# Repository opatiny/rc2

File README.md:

# Remote Control Cylinder

---
Link to "site": https://opatiny.github.io/rc2/.

__WARNING:__ This README is not the main source of information for this project. A detailled paper can be found [here](https://github.com/opatiny/rc2/blob/master/documentation/RemoteControlCylinder.pdf).

_Final cylinder prototype_

## Cite this repository

Océane Patiny, & Luc Patiny. (2020, October 3). opatiny/rc2: Remote controlled cylinder final documentation (Version v1.0.0). Zenodo. http://doi.org/10.5281/zenodo.4064763

## Abstract
This one year project consists in the development of a remote controlled cylinder that uses servo motors to displace its center of mass, which leads the cylinder to accelerate linearly. This implies that very diversified fields such as mathematics, physics, programming, electronics and mechanics had to be explored and partly understood to be combined in the final prototype. This prototype has an acrylic glass base structure with a diameter of 32 cm, it is controlled using a C.H.I.P. Pro (a micro-controller similar to Raspberry Pi) and a customized dedicated extension board. The board includes a driver for four servo motors and a 6 axis accelerometer. Finally, the power supply consists of a pack of three AA batteries. All the programming was made using JavaScript scripts that are run using Node.js and a Shell. In addition, the cylinder is remotely controlled through a web page, which make it easy and intuitive for the user. The final features of this robotic cylinder are the following: it can roll forwards and backwards, stop and keep itself balanced on a gentle slope . Also, it is only working well on flat, hard surfaces, though it could easily be adapted to rougher surfaces. The possibility has also been considered of creating a sphere that uses the same technologies as the cylinder that was constructed in this project. The results of the project can be seen easily in [this movie](https://youtu.be/QggOjoGjJhA).

## Liscence

Finally, this work is meant to be as open-source as possible. Therefore, the software that was developed is under MIT licence, whereas the hardware is under CERN OHL.

## Concept

Initially the project was inspired by a rover realized by [Octanis](https://www.octanis.org/), a student's association specialized in electronics. The rover was supposed to be send to Antarctica and be able to analyse it's environment autonomously. Seeing the Rover tested on a Glacier on a windy day made me wonder what would be the best design for a windproof robot and I immediately thought of a spherical robot. However, once I got back home and looked for similar ideas, I realized that they were already existing projects that consisted in a spherical robot. One of the most famous being the [Sphero](https://www.sphero.com/), a spherical robot toy.

Looking further, I also realized that most of the projects use a similar approach to move the sphere: I call it the hamster wheel approach. It basically is a little car which wheels lay on the outer, rigid shell that induces the movement. I, on the contrary, had imagined a completely different system: I would displace the center of mass of the cylinder to make it roll.

## Programming

All the code that allows the control of the cylinder is contained in the following repository:
[https://github.com/opatiny/rpi-cylinder](https://github.com/opatiny/rpi-cylinder).

The programming has been done in JavaScript (using Node.js) and HTML for the web page that allows the control of the cylinder. Websocket was used to make the web page dynamic.

## Documentation

You can find a lot mor documentation about this project in the [documentation](https://github.com/opatiny/rc2/tree/master/documentation) section of this repository. There, you will find pictures, a developed abstract, and the paper about this project.

## Videos

Cardboard model of the cylinder's mechanism: [https://youtu.be/4SuPhpwOK5g](https://youtu.be/4SuPhpwOK5g)

The mass of cylinderPrototype2 moving on a circle using an atMega32u4: [https://youtu.be/1zOCNZ_r5pY](https://youtu.be/1zOCNZ_r5pY)

Final cylinder's prototype presentation video:
[https://youtu.be/QggOjoGjJhA](https://youtu.be/QggOjoGjJhA)

## Repository structure

In this section, we explain what the different folders of this repository contain and what it was used for.

__Note:__ Three main prototypes were built during this project. To refer to them, we use the acronyms cp1, cp2 and cp3 ("cp" stands for "cylinderPrototype"). You can see pictures of the prototypes in the [Pictures section](#pictures).

### arduino
Very basic programs in Arduino that allowed to test the movement of the mass with cp2. The values of the angles of the servos motors depending on the mass position were exported from the [GeoGebra model](https://github.com/opatiny/rc2/blob/master/movingMassOnCircle/geogebra/cylinderPrototype2/cylinderPrototype2.ggb) that we designed.

### datasheets
Datasheets of the electronical components used in this project: servo motors (MG995), accelerometer (MPU6050), servos driver (PCA9685) and C.H.I.P..

### documentation
Main source of information about this project, contains a pdf of the paper, a presentation, posters and an abstract. You will also find pictures there.

### freecad
FreeCAD is the software we used to create the designs of the cylinder. The "exports" subfolder contains files that can be directly used to laser cut the different parts (.dxf).

### javascript
First JavaScript programs that implemented the mathematical formula that returns the angles of the servos depending on the position of the mass. This code is the base of the [chip](https://github.com/opatiny/chip) GitHub repository, which contains the final code.

### movingMassOnCircle
Contains the GeoGebra models of the cylinder's mass movement and files commenting the observations made based upon them.

### pcb
Contains the Eagle and KiCAD files of the extension boards. They are two different boards, because when working on the project after a year, I realized that the cylinder was no longer functionning. I therefore had to change the micro-controller, because C.H.I.P. had made bankrupt. I decided to switch to a Raspberry Pi Nano W.

### raspberry
Procedure allowing to format a Raspberry Pi to make it act as a WiFi rooter.

## Pictures

Here are a few pictures of the project.

_Cardboard model of the cylinder_

_First prototype of the cylinder_

_[GeoGebra](https://www.geogebra.org/) model allowing to see the movement of the servo motors_

_Close-up of the second prototype_

_Metal turning a part of cp3_

_PCB extension allowing the connection of two I2C peripherals to the C.H.I.P. Pro (accelerometer and servo driver)_

_Long aperture picture of the mass moving on a spiral (cp3), max radius is 40mm_

_Final control web page_

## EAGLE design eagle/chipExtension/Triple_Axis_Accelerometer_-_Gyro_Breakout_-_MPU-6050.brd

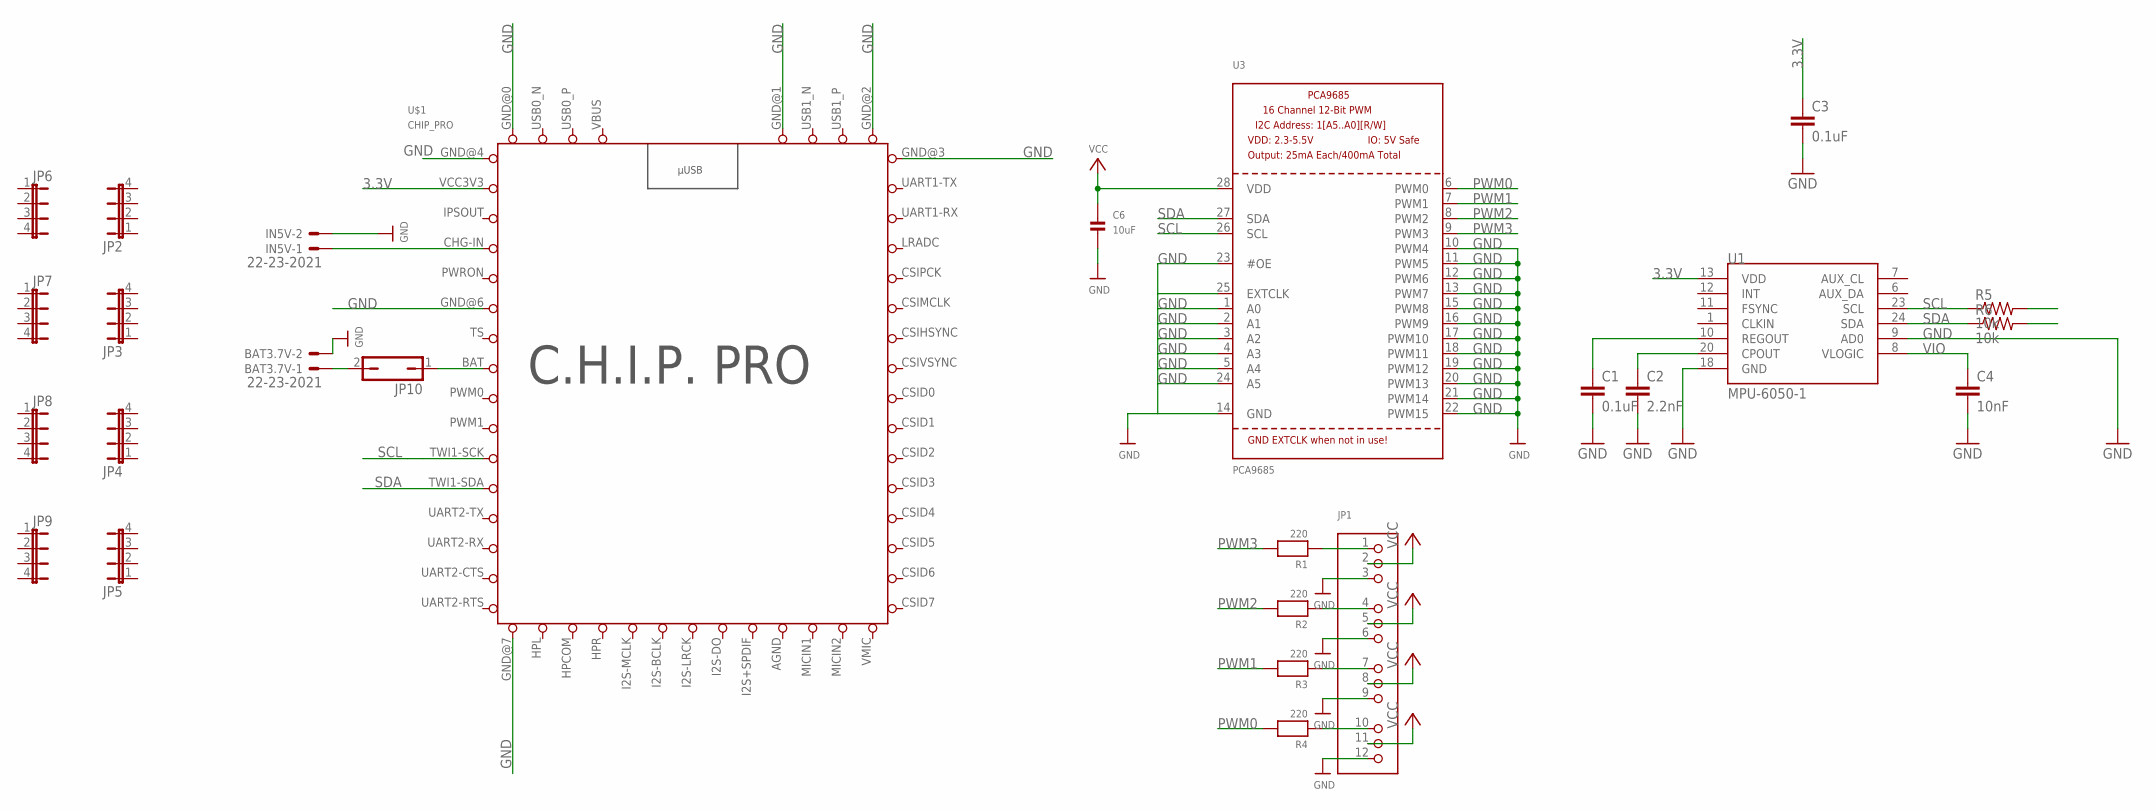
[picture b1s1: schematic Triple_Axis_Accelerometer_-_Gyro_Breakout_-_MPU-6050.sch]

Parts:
BAT3.7V: 22-23-2021
C1, C3: 0.1uF; 0603-CAP
C2: 2.2nF; 0603-CAP
C4: 10nF; 0603-CAP
C6: 10uF; 0805
IN5V: 22-23-2021
JP1: HEADER-3X04; 3X04
JP2, JP3, JP4, JP5, JP6, JP7, JP8, JP9: JP4E; JP4
JP10: JP1Q; JP1
R1, R2, R3, R4: 220; 0805
R5, R6: 10k; R0805
U1: MPU-6050-1; QFN-24-4MM2
U3: PCA9685; TSSOP28
U$1: CHIP_PRO

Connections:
3.3V: C3.1, U1.13 (VDD), U$1.VCC3V3
AGND: U$1.AGND
GND: BAT3.7V.2, C1.2, C2.2, C3.2, C4.2, C6.2, IN5V.2, JP1.3, JP1.6, JP1.9, JP1.12, U1.9 (AD0), U1.18 (GND), U3.1 (A0), U3.2 (A1), U3.3 (A2), U3.4 (A3), U3.5 (A4), U3.10 (PWM4), U3.11 (PWM5), U3.12 (PWM6), U3.13 (PWM7), U3.14 (GND), U3.15 (PWM8), U3.16 (PWM9), U3.17 (PWM10), U3.18 (PWM11), U3.19 (PWM12), U3.20 (PWM13), U3.21 (PWM14), U3.22 (PWM15), U3.23 (#OE), U3.24 (A5), U3.25 (EXTCLK), U$1.GND@0 (GND), U$1.GND@1 (GND), U$1.GND@2 (GND), U$1.GND@3 (GND), U$1.GND@4 (GND), U$1.GND@6 (GND), U$1.GND@7 (GND)
IPSOUT: U$1.IPSOUT
unnamed: JP1.1, R1.1
unnamed: JP1.4, R2.1
unnamed: C2.1, U1.20 (CPOUT)
unnamed: JP1.7, R3.1
unnamed: C1.1, U1.10 (REGOUT)
unnamed: JP1.10, R4.1
unnamed: IN5V.1, U$1.CHG-IN
PWM0: R4.2, U3.6 (PWM0)
PWM1: R3.2, U3.7 (PWM1)
PWM2: R2.2, U3.8 (PWM2)
PWM3: R1.2, U3.9 (PWM3)
SCL: R5.1, R5.2, U1.23 (SCL), U3.26 (SCL), U$1.TWI1-SCK
SDA: R6.1, R6.2, U1.24 (SDA), U3.27 (SDA), U$1.TWI1-SDA
VBUS: U$1.VBUS
VCC: BAT3.7V.1, C6.1, JP1.2, JP1.5, JP1.8, JP1.11, JP10.1, JP10.2, U3.28 (VDD), U$1.BAT
VIO: C4.1, U1.8 (VLOGIC)

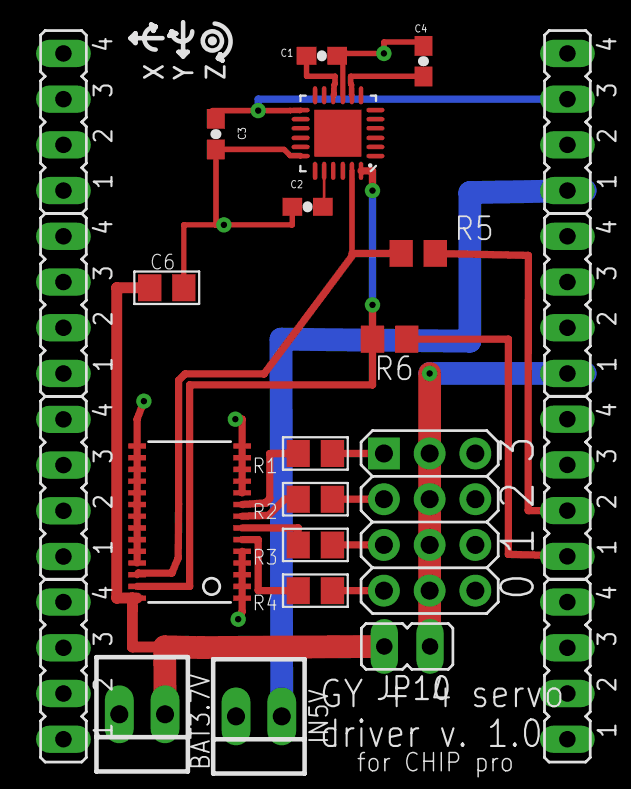
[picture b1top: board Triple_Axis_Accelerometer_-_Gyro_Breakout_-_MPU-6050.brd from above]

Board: 2 copper layers, 26 parts (1 on the bottom side), 17 nets.

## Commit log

2016-10-17 Datasheet MPU-6050 accelerometer - gyroscope
2016-10-17 Add initial freecad files
2016-10-17 Add servo oscilloscope
2016-10-19 Add high speed
2016-11-28 reorganising directories
2016-11-28 move files
2016-11-28 editing the readme
2016-11-28 readme changes
2016-12-19 Ordering directories
2016-12-19 add convert wolfram
2016-12-20 fix bug of ) ( not converted to ) * (
2016-12-30 working on code and adding .idea
2016-12-30 testing committing
2017-01-05 adding pictures
2017-01-16 modifing formula code
2017-01-18 modifing freecad document: wheel
2017-01-21 adding cylinder schemes in pictures
2017-01-29 modifing wheel and wheelAccessory (freecad)
2017-02-11 add gitignore file
2017-02-11 Remove unused files
2017-02-11 Add test code for understand code
2017-02-11 trying to understand formulas in code
2017-02-13 new formula taken from wolfram
    the thee other ones are when the general signs varies and when the sign in the cos varies
2017-02-22 adding links to the README
2017-02-24 Ordering pictures
2017-04-03 Adding new geogebra file. This is a first test of sovling the angles of the servo depending on the mass position, graphicaly.
2017-04-03 Adding datasheets
2017-04-05 Working on servosMovement
2017-04-05 Developing servos angles depending on position of the mass
2017-04-05 Adding "mess".
2017-04-08 First working moving servos
2017-04-10 Evolving servoMovement and adding pictures
2017-04-10 Adding presiceServoAxisTest text files
2017-04-10 Finally finding the limitation of the servo axis length!
2017-05-21 Adding physics and calculusScheme
2017-06-06 Modifing calculusScheme.key and adding squaredSquare
2017-06-18 Adding datasheets for alreadyExisting and working on circleAroundCenter with the geogebra approach.
2017-06-19 Adding pictures of prototype2 and upgrading calculusScheme.key.
2017-06-30 Organising movingMassOnCircle and adding schemes.
2017-06-30 Working on code
2017-07-03 Making the javascript code to have srevos angles depending on mass angle or position.
2017-07-03 Ordering files and adding pictures
2017-07-03 add ternary operator
2017-07-04 working on movingMassOnCircle
2017-07-04 work in progress
2017-07-06 Modifing cylinderDataKeynote.
2017-07-12 Working on eagle.
2017-07-13 Adding holes to the PCB on eagle and enhancing the freeca model of cylinder prototype 3.
2017-07-14 Adding jumper to eagle files and enhancing the freecad model of cylinderPrototype3.
2017-07-15 improve eagle design
2017-07-21 adapt the commandLineFunctions to cylinderPrototype3
2017-07-22 add pictures and modify keynotes.
2017-07-23 modify cylinderDataKeynote
2017-07-24 add rapporteur.pdf to pictures.
2017-08-16 add the pdf of speedFunctionScheme.
2017-08-18 adapt the javascript function returnAngleOnMassAngle.js to export values to spreadsheet
2017-08-18 add the keynote related to the pcb
2017-08-20 upgrade mess
2017-09-10 modify infos that come with the geogebra data
2017-09-22 add picture to parametersTest to test if d can be bigger than R
2017-09-24 add many screenshots of the keynote documents
2017-10-01 ordering pdfs of keynote, modifying approach.key
2017-10-08 clean freecad
2017-10-09 add all export files from freecad
2017-10-10 add pdfs of freecad files, add laserCutter keynote
2017-10-13 Create LICENSE
2017-10-16 mainly modify with keynote exports
2017-10-29 work on keynotes
2017-10-29 work on keynote files
2017-11-01 add communicationSystem.key and modify geogebra model of cp2
2017-11-01 add web page pictures
2017-11-19 order whole git and suppress not important pictures
2019-03-02 add kicad of rpi extension
2019-03-03 add kicad extension
2019-03-03 add readme for rpi
2019-03-03 update procedure to install node
2019-03-05 started posters for SAJ
2019-03-07 work on posters
2019-03-10 update kicad for extension
2019-03-10 remove gerber files
2019-03-11 add image smallLed.pdf and pdf of oral presentation
2019-03-13 rearrange repo and work on README
2019-03-13 test commit
2019-03-15 remove useless files
2019-03-25 add documentation/speedResults
2019-03-25 add final compressed pdf to documentation
2019-03-26 work on documentation, add abstract
2019-03-28 Set theme jekyll-theme-minimal
2019-03-28 Set theme jekyll-theme-slate
2019-04-01 add Rdata and Rhistory in gitignore
2019-04-01 update poster and remove useless files
2019-04-02 enhance README
2019-04-02 remove renamed files
2019-04-04 finish posters
2019-04-04 replace poster keynote by pdf
2019-04-04 rename poster pdf file
2019-04-12 rename posters pdf and add flyer
2019-04-17 enhance raspberry doc
2019-07-08 update paper pdf
2019-09-06 Add files via upload
    svg and dxf files of cp3
2020-10-03 update readme link
2020-10-03 add citation to readme
